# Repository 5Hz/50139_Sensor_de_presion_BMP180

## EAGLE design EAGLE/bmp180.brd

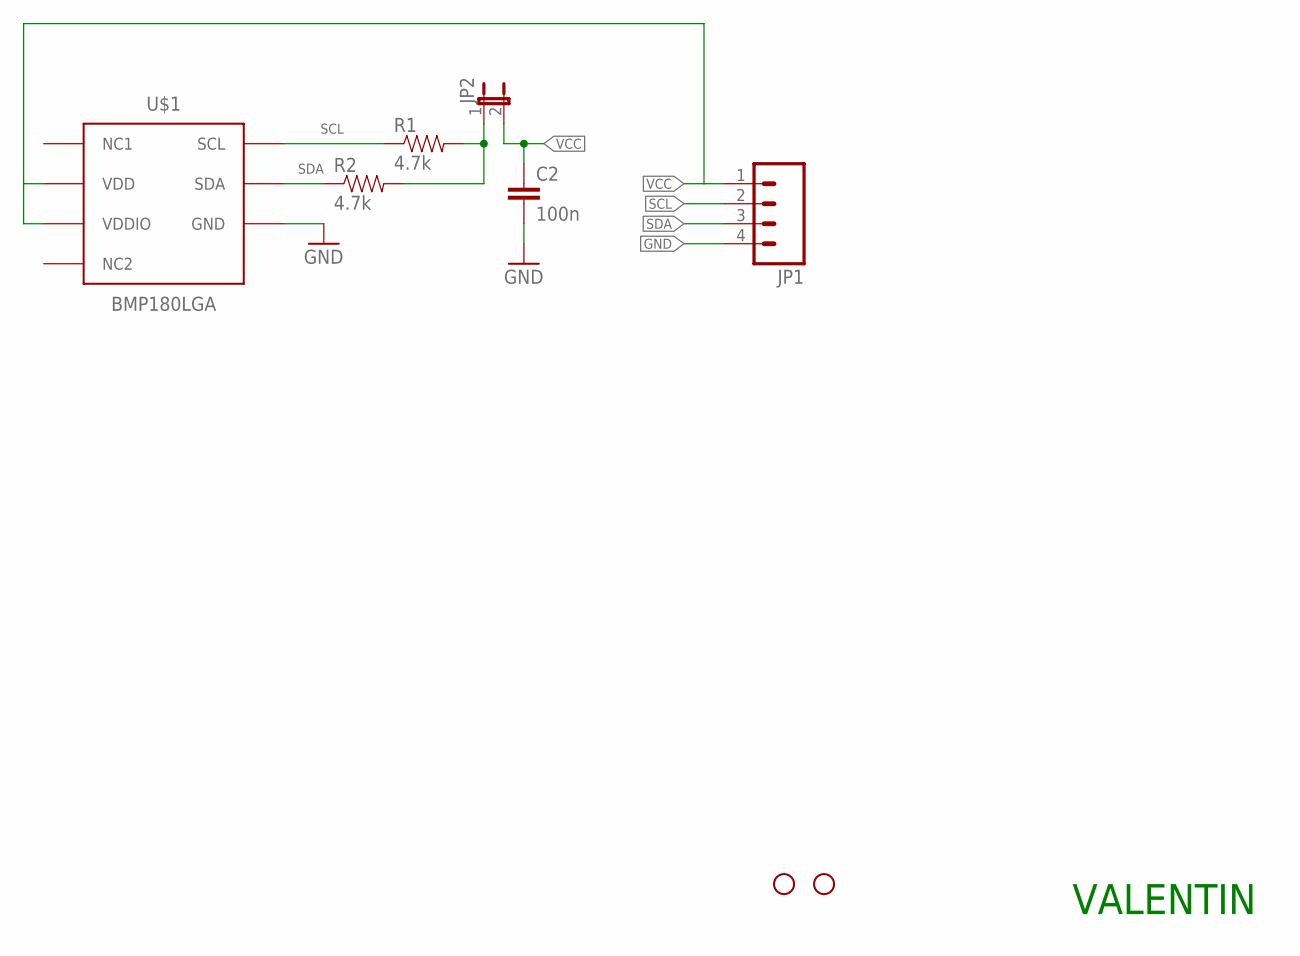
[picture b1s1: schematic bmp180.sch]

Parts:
C2: 100n; 0603-CAP
JP1: M04PTH; 1X04
JP2: JUMPER-2SMD-NO; SJ_2S-NO
JP3, JP4: STAND-OFFTIGHT; STAND-OFF-TIGHT
R1, R2: 4.7k; 0603-RES
U$1: BMP180LGA; BMP180_LGA

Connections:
ASDF: JP2.1, R1.2, R2.2
GND: C2.2, JP1.4, U$1.P$7 (GND)
SCL: JP1.2, R1.1, U$1.P$5 (SCL)
SDA: JP1.3, R2.1, U$1.P$6 (SDA)
VCC: C2.1, JP1.1, JP2.2, U$1.P$2 (VDD), U$1.P$3 (VDDIO)

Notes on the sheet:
VALENTIN

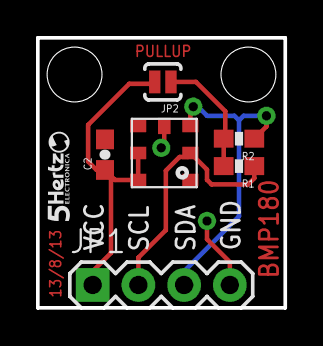
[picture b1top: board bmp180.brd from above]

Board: 2 copper layers, 13.7 x 15.0 mm, 9 parts (0 on the bottom side), 5 nets.

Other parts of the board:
U$2: 5HZ_LOGO_H_5MM

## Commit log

2014-01-14 creación

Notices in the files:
parts and their libraries:
SparkFun: Licensing: CC v3.0 Share-Alike You are welcome to use this library for commercial purposes.
